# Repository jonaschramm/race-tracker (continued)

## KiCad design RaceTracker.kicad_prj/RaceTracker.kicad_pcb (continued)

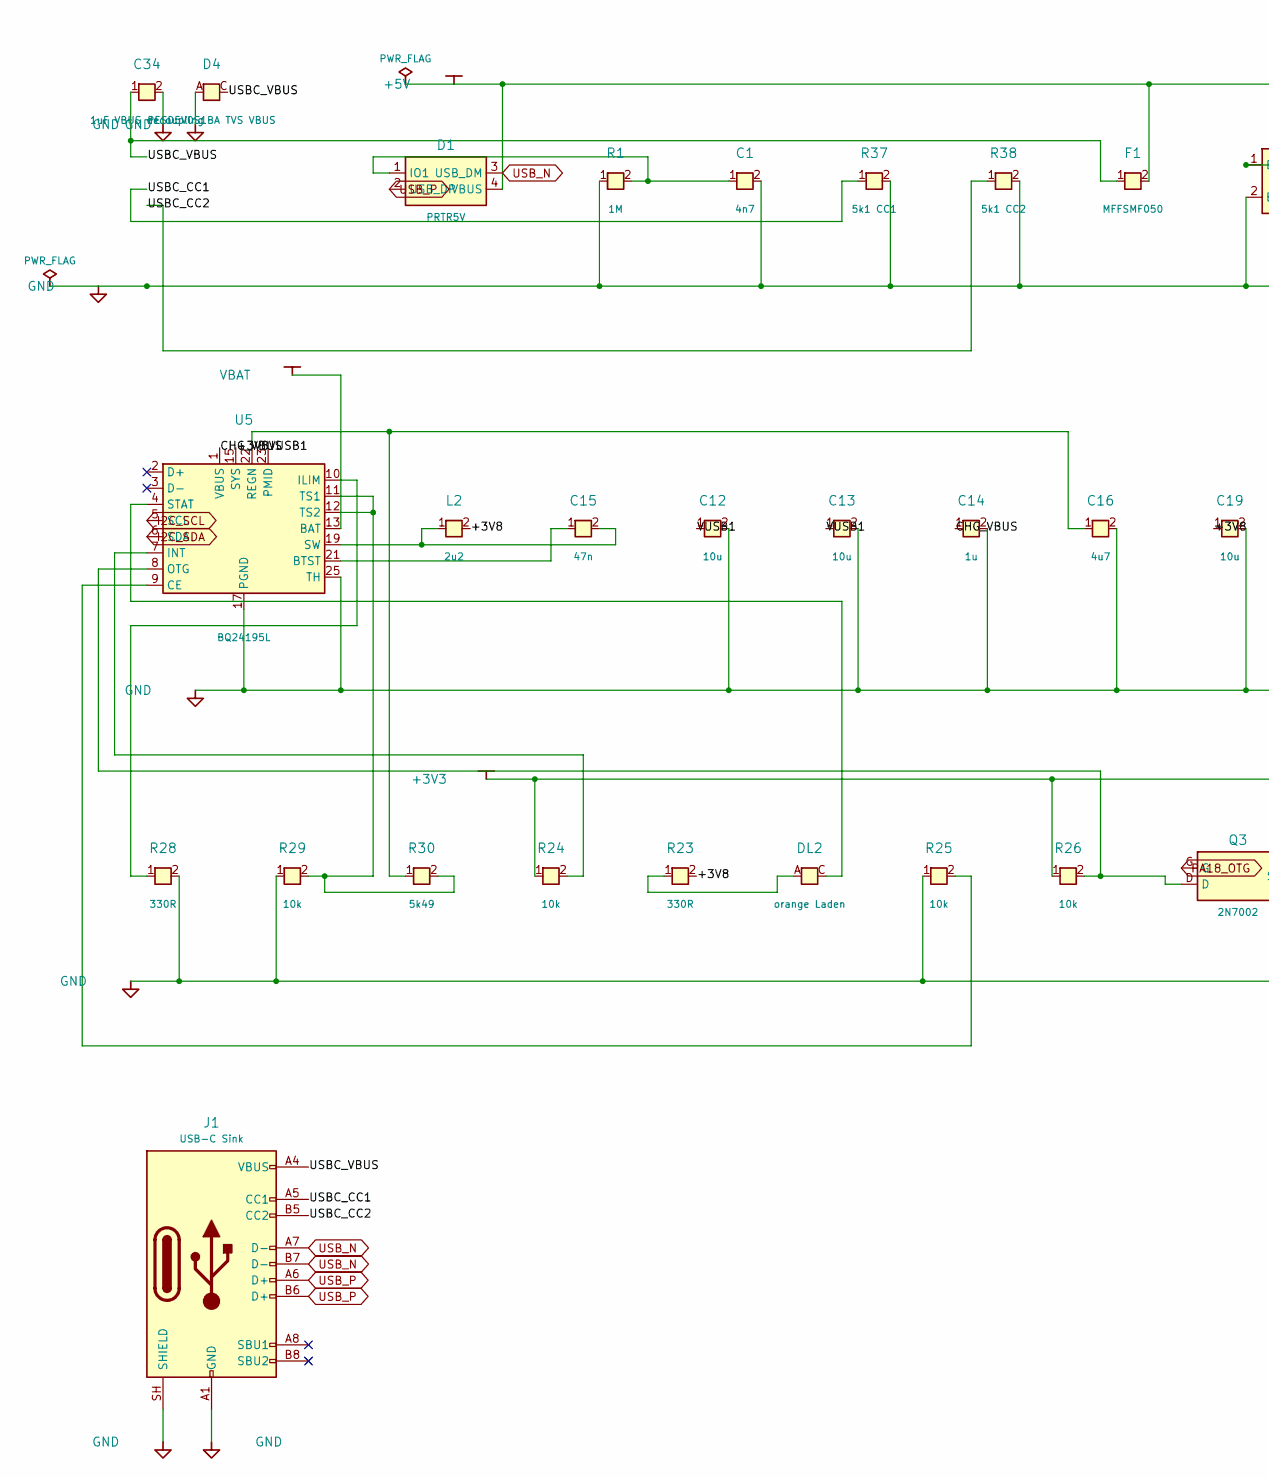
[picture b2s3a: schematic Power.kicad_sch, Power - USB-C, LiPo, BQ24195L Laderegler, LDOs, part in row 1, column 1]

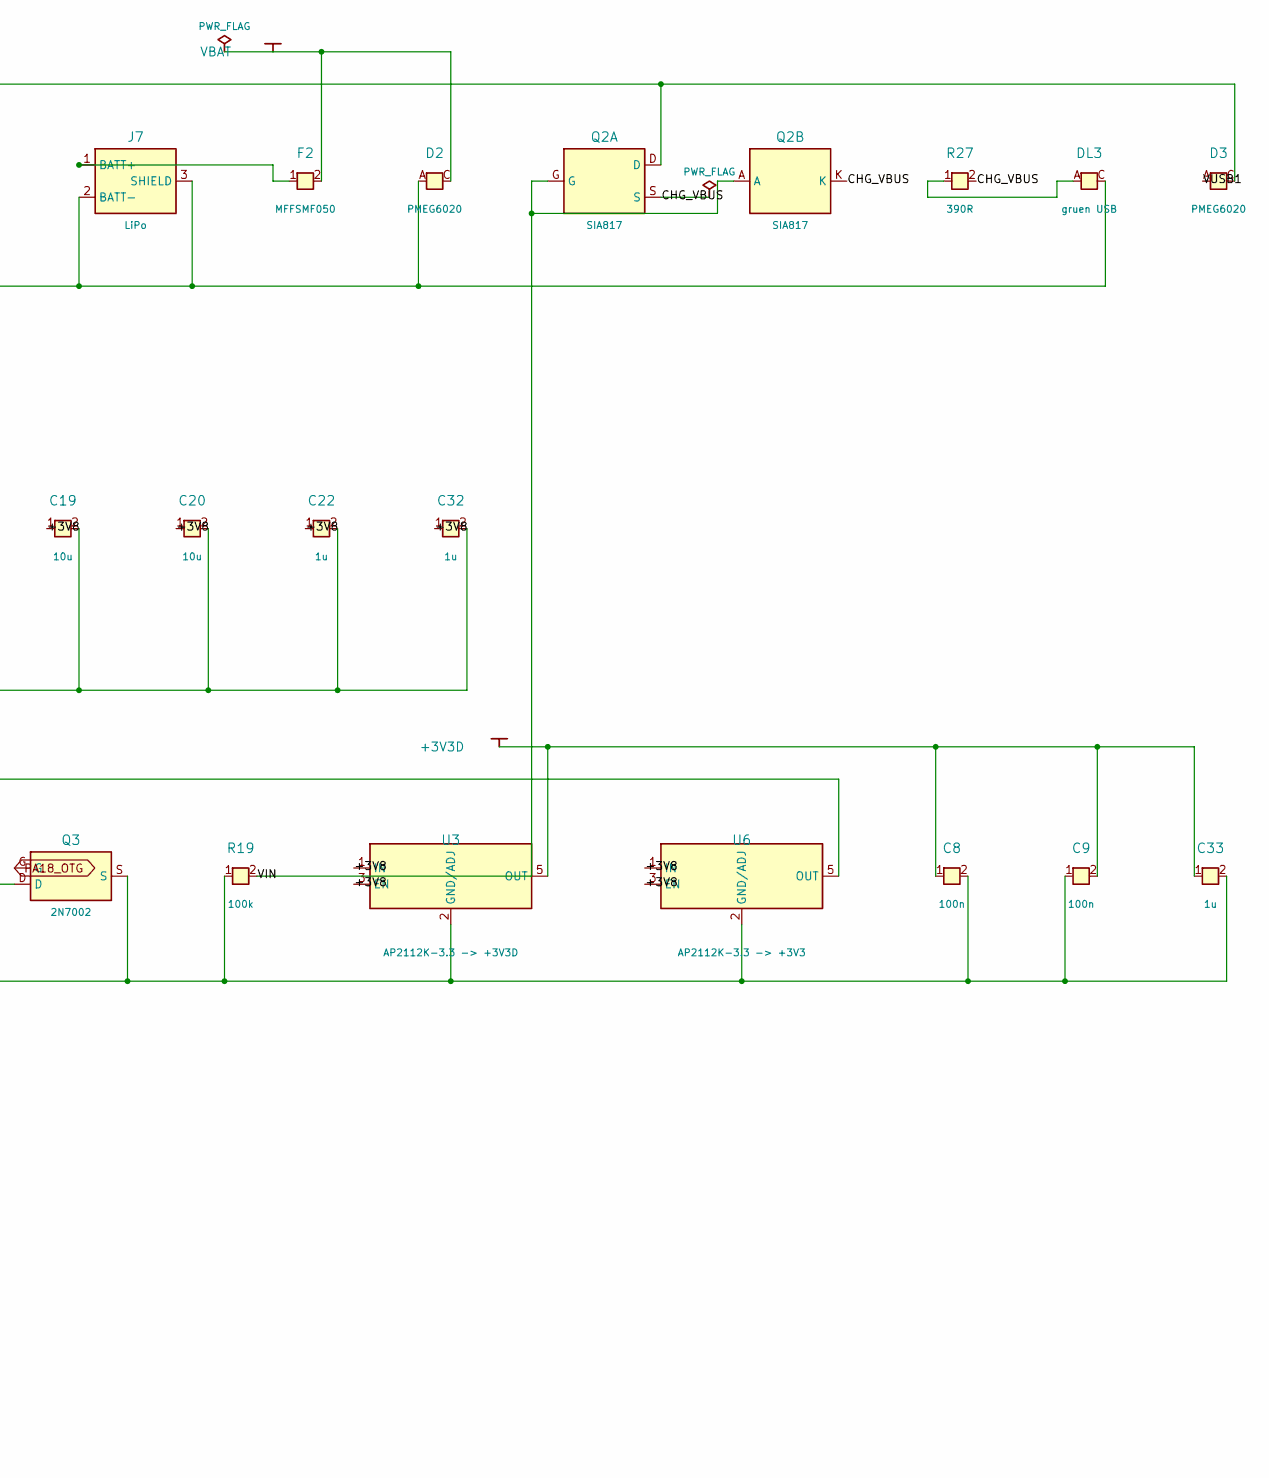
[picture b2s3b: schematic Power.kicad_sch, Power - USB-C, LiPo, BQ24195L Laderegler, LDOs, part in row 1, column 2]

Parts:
C1: 4n7; C_0805_2012Metric
C8, C9: 100n; C_0402_1005Metric
C12, C13, C19, C20: 10u; C_0603_1608Metric
C14, C22, C32, C33: 1u; C_0402_1005Metric
C15: 47n; C_0402_1005Metric
C16: 4u7; C_0402_1005Metric
C34: 1uF VBUS decoupling; C_0402_1005Metric
D1: PRTR5V; SOT143B_4N; MPN PRTR5V0U2X,215
D2, D3: PMEG6020; SODFL3517X110N
D4: PESD5V0S1BA TVS VBUS; D_SOD-323; MPN PESD5V0S1BA
DL2: orange Laden; LED_0603_AK
DL3: gruen USB; LED_0603_AK
F1, F2: MFFSMF050; Fuse_0603_1608Metric
J1: USB-C Sink; USB_C_Receptacle_HRO_TYPE-C-31-M-12; MPN TYPE-C-31-M-12
J7: LiPo; JST_S2B_PH_SM4_TB
L2: 2u2; SRP4020
Q2: SIA817; SON65P205X205X75-8N-MWSD
Q3: 2N7002; SOTFL50P160X78-3
R1: 1M; R_0402_1005Metric
R19: 100k; R_0402_1005Metric
R23, R28: 330R; R_0402_1005Metric
R24, R25, R26, R29: 10k; R_0402_1005Metric
R27: 390R; R_0402_1005Metric
R30: 5k49; R_0402_1005Metric
R37: 5k1 CC1; R_0402_1005Metric
R38: 5k1 CC2; R_0402_1005Metric
U3: AP2112K-3.3 -> +3V3D; SOT25
U5: BQ24195L; QFN24_BQ24195L
U6: AP2112K-3.3 -> +3V3; SOT25

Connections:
+3V3D: C8.1, C9.2, C33.1, U3.5 (OUT); also elsewhere on the board
/Power/+3V8: C19.1, C20.1, C22.1, C32.1, L2.2, R23.2, U3.1 (IN), U3.3 (EN), U5.15 (SYS), U5.16, U6.1 (IN), U6.3 (EN)
/Power/CHG_VBUS: C14.1, Q2.K, Q2.K2, Q2.S, R27.2, U5.1 (VBUS), U5.24
/Power/USBC_CC1: J1.A5 (CC1), R37.1
/Power/USBC_CC2: J1.B5 (CC2), R38.1
/Power/USBC_VBUS: C34.1, D4.C, F1.1, J1.A4 (VBUS), J1.A9 (VBUS), J1.B4 (VBUS), J1.B9 (VBUS)
/Power/VIN: Q2.A, Q2.G, R19.2
/Power/VUSB1: C12.1, C13.1, D3.A, U5.23 (PMID)
GND: C1.2, C8.2, C9.1, C12.2, C13.2, C14.2, C16.2, C19.2, C20.2, C22.2, C32.2, C33.2, C34.2, D2.A, D4.A, DL3.C, J1.A1 (GND), J1.A12 (GND), J1.B1 (GND), J1.B12 (GND), J1.SH (SHIELD), J7.2 (BATT-), J7.3 (SHIELD), J7.4 (SHIELD), Q3.S, R1.1, R19.1, R25.1, R28.2, R29.1, R37.2, R38.2, U3.2 (GND/ADJ), U5.17 (PGND), U5.18, U5.25 (TH), U6.2 (GND/ADJ); also elsewhere on the board
I2C_SCL: U5.5 (SCL); also elsewhere on the board
I2C_SDA: U5.6 (SDA); also elsewhere on the board
unnamed: C1.1, D1.1 (IO1), R1.2
unnamed: DL2.A, R23.1
unnamed: DL3.A, R27.1
unnamed: F2.1, J7.1 (BATT+)
unnamed: C15.1, U5.21 (BTST)
unnamed: R25.2, U5.9 (CE)
unnamed: R28.1, U5.10 (ILIM)
unnamed: R24.2, U5.7 (INT)
unnamed: Q3.D, R26.2, U5.8 (OTG)
unnamed: C16.1, R30.1, U5.22 (REGN)
unnamed: DL2.C, U5.4 (STAT)
unnamed: C15.2, L2.1, U5.19 (SW), U5.20
unnamed: R29.2, R30.2, U5.11 (TS1), U5.12 (TS2)
PA18_OTG: Q3.G; also elsewhere on the board
USB_P: D1.2 (USB_DP), J1.A6 (D+), J1.B6 (D+); also elsewhere on the board
VBAT: D2.C, F2.2, U5.13 (BAT), U5.14; also elsewhere on the board

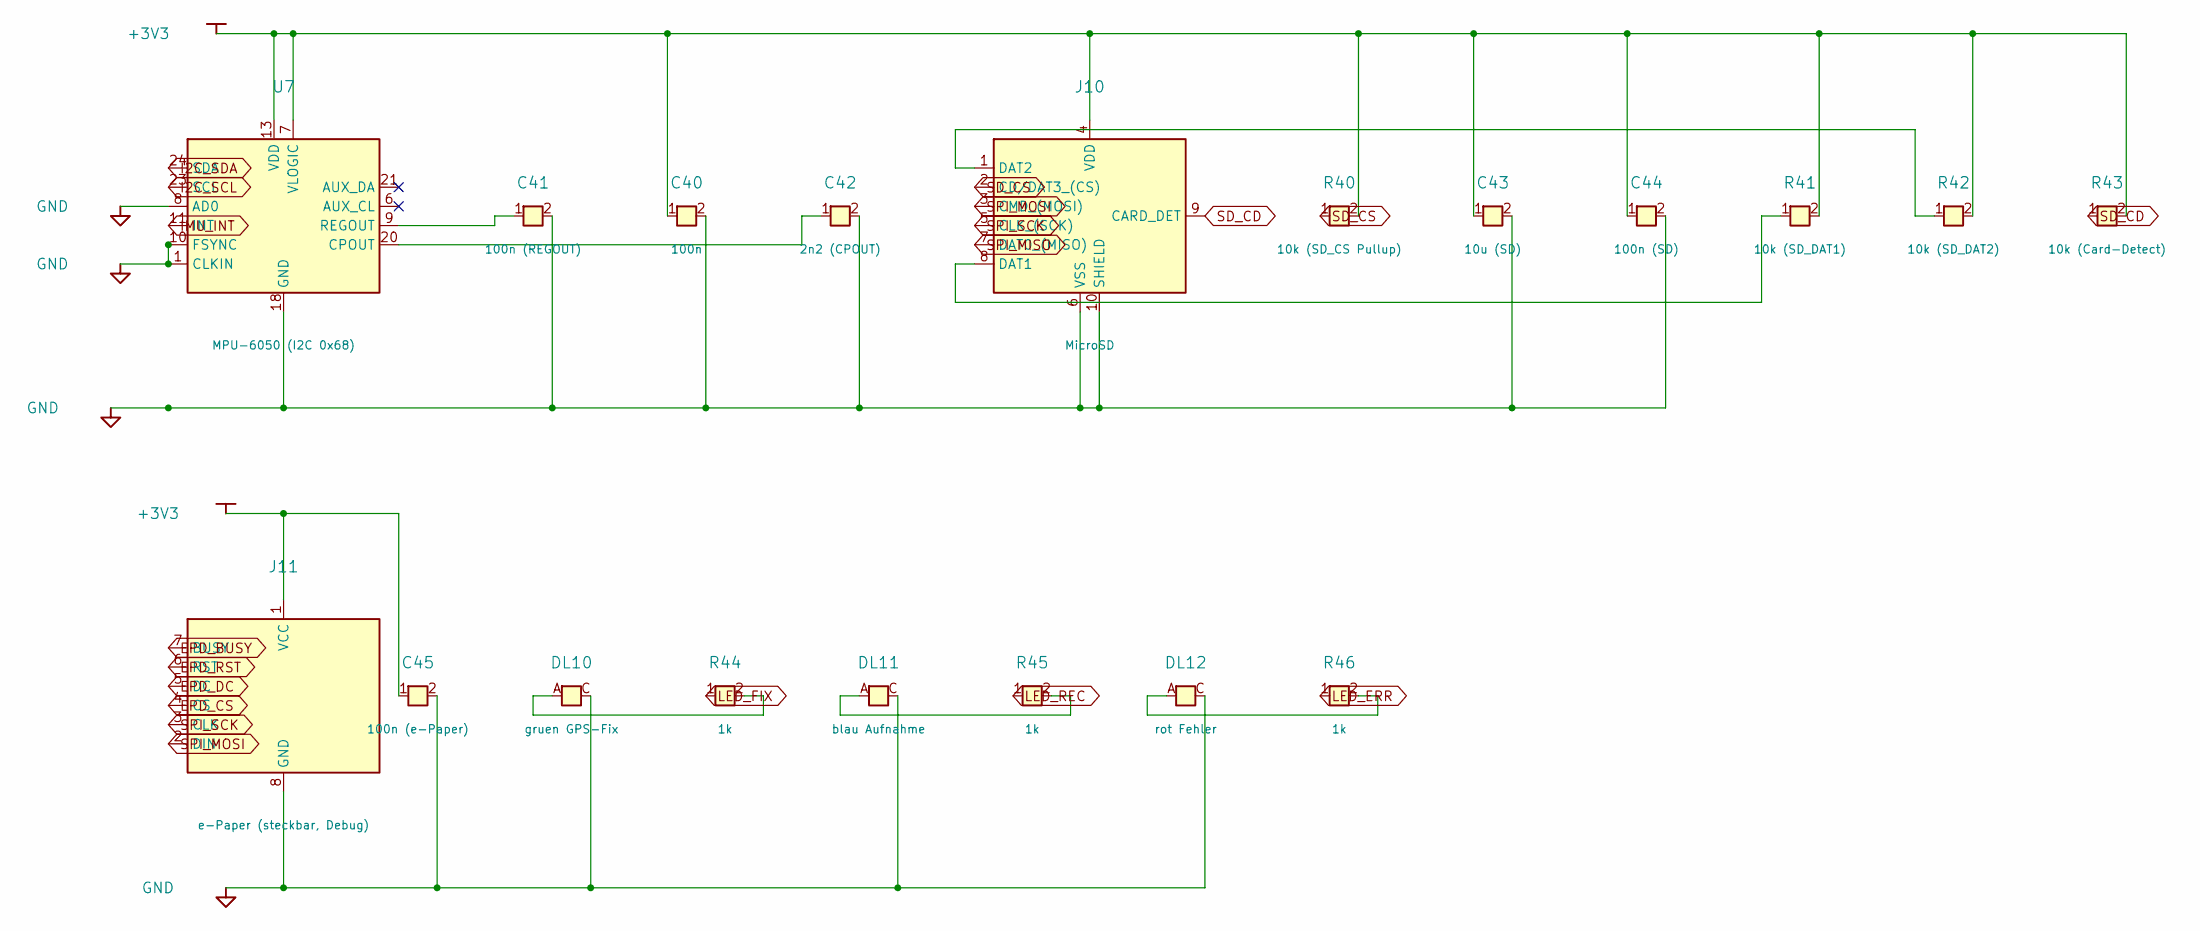
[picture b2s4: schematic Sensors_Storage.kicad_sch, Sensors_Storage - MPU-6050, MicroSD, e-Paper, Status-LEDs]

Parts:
C40: 100n; C_0402_1005Metric
C41: 100n (REGOUT); C_0402_1005Metric
C42: 2n2 (CPOUT); C_0402_1005Metric
C43: 10u (SD); C_0603_1608Metric
C44: 100n (SD); C_0402_1005Metric
C45: 100n (e-Paper); C_0402_1005Metric
DL10: gruen GPS-Fix; LED_0603_AK
DL11: blau Aufnahme; LED_0603_AK
DL12: rot Fehler; LED_0603_AK
J10: MicroSD; microSD_HC_Molex_104031-0811
J11: e-Paper (steckbar, Debug); PinHeader_1x08_P2.54mm_Vertical
R40: 10k (SD_CS Pullup); R_0402_1005Metric
R41: 10k (SD_DAT1); R_0402_1005Metric
R42: 10k (SD_DAT2); R_0402_1005Metric
R43: 10k (Card-Detect); R_0402_1005Metric
R44, R45, R46: 1k; R_0402_1005Metric
U7: MPU-6050 (I2C 0x68); InvenSense_QFN-24_4x4mm_P0.5mm

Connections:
EPD_BUSY: J11.7 (BUSY); also elsewhere on the board
EPD_CS: J11.4 (CS); also elsewhere on the board
EPD_DC: J11.5 (DC); also elsewhere on the board
EPD_RST: J11.6 (RST); also elsewhere on the board
GND: C40.2, C41.2, C42.2, C43.2, C44.2, C45.2, DL10.C, DL11.C, DL12.C, J10.6 (VSS), J10.10 (SHIELD), J11.8 (GND), U7.1 (CLKIN), U7.8 (AD0), U7.10 (FSYNC), U7.18 (GND); also elsewhere on the board
I2C_SCL: U7.23 (SCL); also elsewhere on the board
I2C_SDA: U7.24 (SDA); also elsewhere on the board
IMU_INT: U7.11 (INT); also elsewhere on the board
LED_ERR: R46.1; also elsewhere on the board
LED_FIX: R44.1; also elsewhere on the board
LED_REC: R45.1; also elsewhere on the board
unnamed: DL10.A, R44.2
unnamed: DL11.A, R45.2
unnamed: DL12.A, R46.2
unnamed: J10.8 (DAT1), R41.1
unnamed: J10.1 (DAT2), R42.1
unnamed: C42.1, U7.20 (CPOUT)
unnamed: C41.1, U7.9 (REGOUT)
SD_CD: J10.9 (CARD_DET), R43.1; also elsewhere on the board
SD_CS: J10.2 (CD/DAT3_(CS)), R40.1; also elsewhere on the board
SPI_MISO: J10.7 (DAT0_(MISO)); also elsewhere on the board
SPI_MOSI: J10.3 (CMD_(MOSI)), J11.2 (DIN); also elsewhere on the board
SPI_SCK: J10.5 (CLK_(SCK)), J11.3 (CLK); also elsewhere on the board

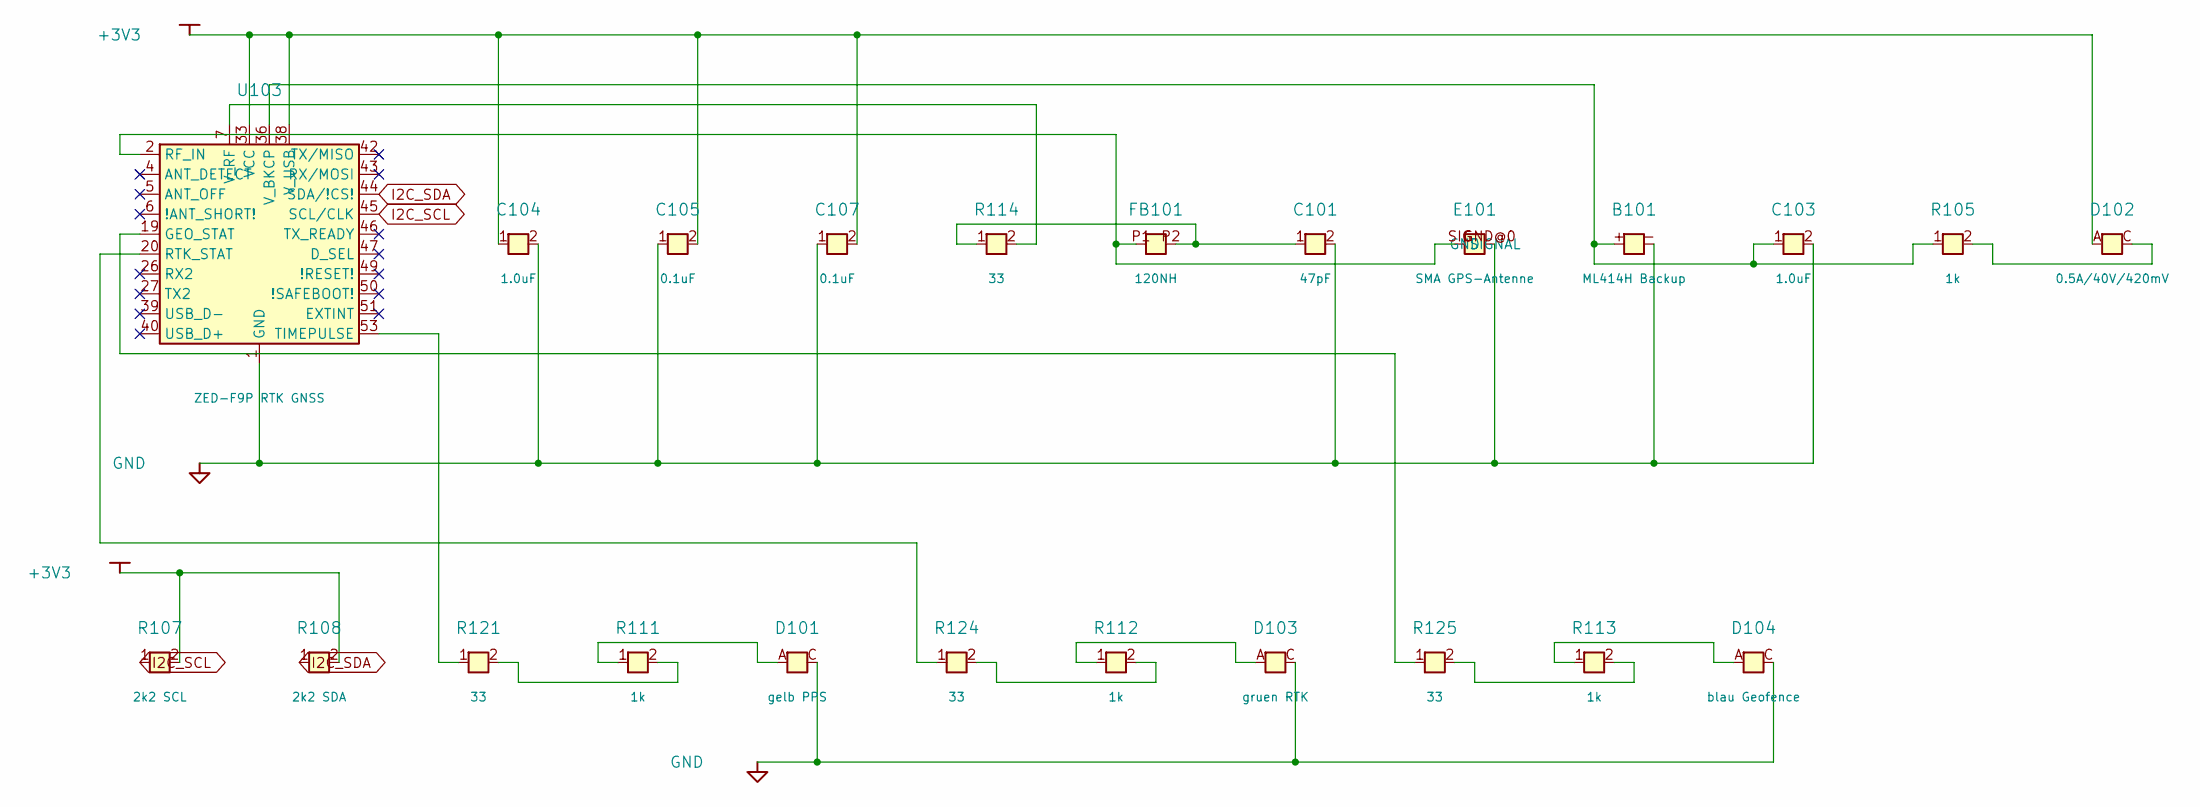
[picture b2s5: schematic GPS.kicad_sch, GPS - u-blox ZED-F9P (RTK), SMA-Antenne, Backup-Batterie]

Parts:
B101: ML414H Backup; ML414H_COIN_CELL
C101: 47pF; C_0402_1005Metric
C103, C104: 1.0uF; C_0402_1005Metric
C105, C107: 0.1uF; C_0402_1005Metric
D101: gelb PPS; LED_0603_AK
D102: 0.5A/40V/420mV; SODFL3517X110N
D103: gruen RTK; LED_0603_AK
D104: blau Geofence; LED_0603_AK
E101: SMA GPS-Antenne; SMA_EDGE
FB101: 120NH; L_0402_1005Metric
R105, R111, R112, R113: 1k; R_0402_1005Metric
R107: 2k2 SCL; R_0402_1005Metric
R108: 2k2 SDA; R_0402_1005Metric
R114, R121, R124, R125: 33; R_0402_1005Metric
U103: ZED-F9P RTK GNSS; ZED_F9P_LGA102

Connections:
GND: B101.-, C101.2, C103.2, C104.2, C105.1, C107.1, D101.C, D103.C, D104.C, E101.GND@0 (GND), E101.GND@1 (GND), E101.GND@2 (GND), E101.GND@3 (GND), U103.1 (GND), U103.3, U103.12, U103.14, U103.32, U103.37, U103.41, U103.48, U103.55, U103.56, U103.57, U103.58, U103.59, U103.60, U103.61, U103.62, U103.63, U103.64, U103.65, U103.66, U103.67, U103.68, U103.69, U103.70, U103.71, U103.72, U103.73, U103.74, U103.75, U103.76, U103.77, U103.78, U103.79, U103.80, U103.81, U103.82, U103.83, U103.84, U103.85, U103.86, U103.87, U103.88, U103.89, U103.90, U103.91, U103.92, U103.93, U103.94, U103.95, U103.96, U103.97, U103.98, U103.99, U103.100, U103.101, U103.102; also elsewhere on the board
I2C_SCL: R107.1, U103.45 (SCL/CLK); also elsewhere on the board
I2C_SDA: R108.1, U103.44 (SDA/!CS!); also elsewhere on the board
unnamed: C101.1, FB101.P2, R114.1
unnamed: D101.A, R111.1
unnamed: D102.C, R105.2
unnamed: D103.A, R112.1
unnamed: D104.A, R113.1
unnamed: E101.SIG (SIGNAL), FB101.P1, U103.2 (RF_IN)
unnamed: R111.2, R121.2
unnamed: R112.2, R124.2
unnamed: R113.2, R125.2
unnamed: R125.1, U103.19 (GEO_STAT)
unnamed: R124.1, U103.20 (RTK_STAT)
unnamed: R121.1, U103.53 (TIMEPULSE)
unnamed: B101.+, C103.1, R105.1, U103.36 (V_BKCP)
unnamed: R114.2, U103.7 (V_RF)

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
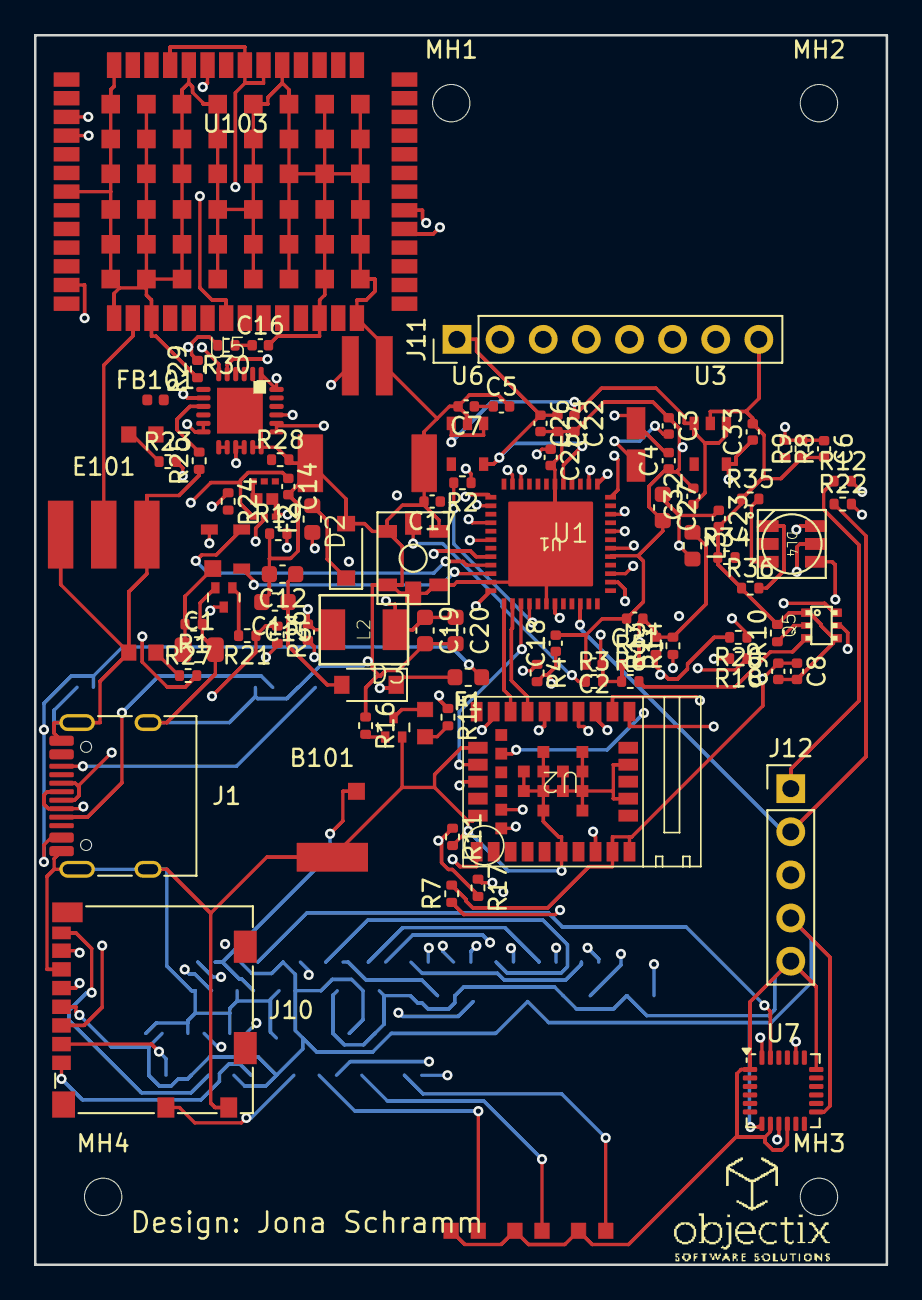
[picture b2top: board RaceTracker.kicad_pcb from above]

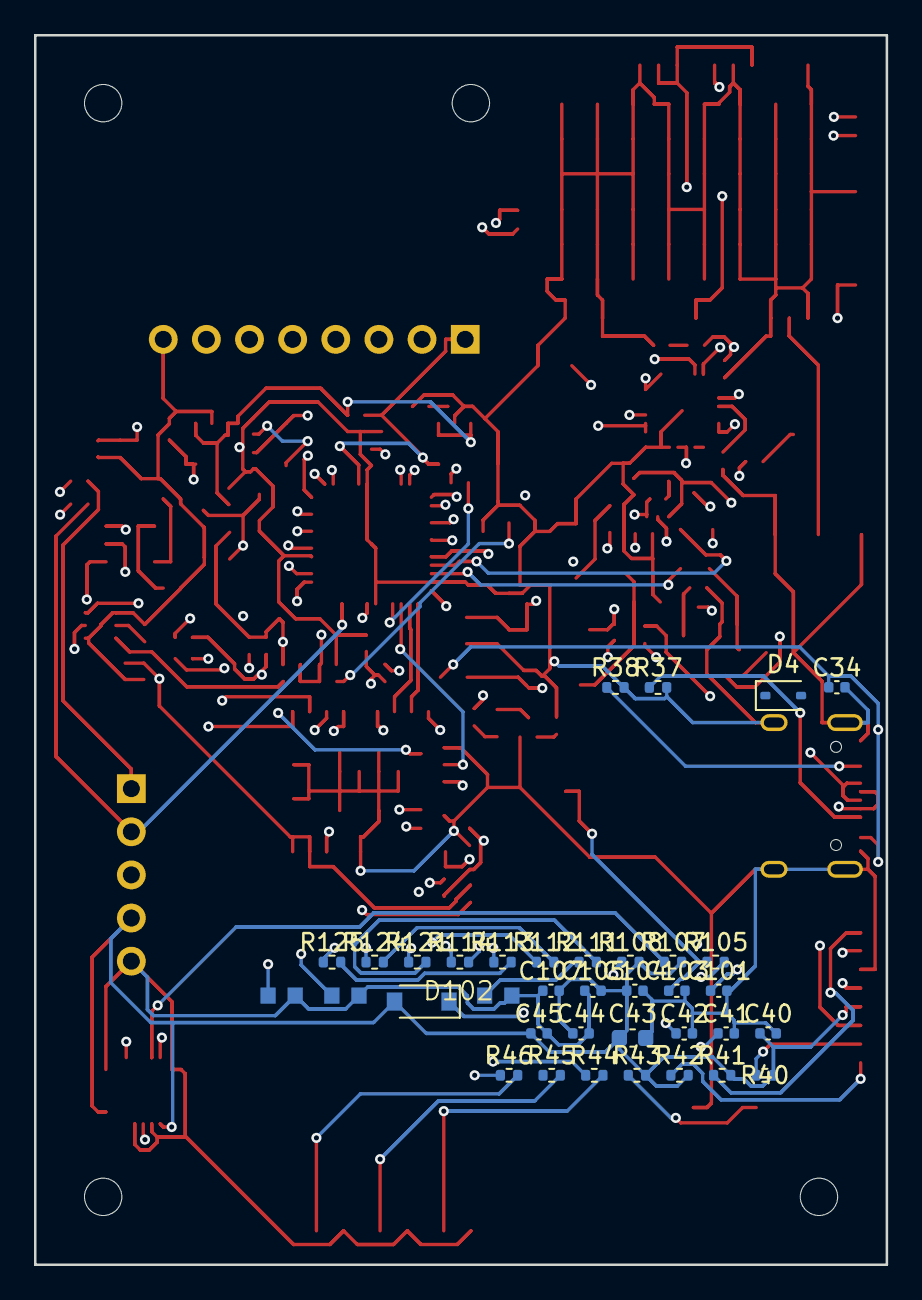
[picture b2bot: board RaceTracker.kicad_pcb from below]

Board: 4 copper layers, 50.2 x 72.4 mm, 135 parts (36 on the bottom side), 101 nets.

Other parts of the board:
MH1, MH2, MH3, MH4: MountingHole_2.2mm_M2

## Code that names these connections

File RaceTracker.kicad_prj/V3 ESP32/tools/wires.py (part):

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tap_label("R11", "1", "+3V3", 0, -STUB)
tap_label("J3", "1", "GND", -STUB, 0)
tap_label("J3", "2", "+3V3", -STUB, 0)
tap_label("J3", "3", "I2C_SDA", STUB, 0)
tap_label("J3", "4", "I2C_SCL", STUB, 0)

# ===========================================================================
# SPI to the microSD socket: same pattern. J4's real pinout interleaves
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# ===========================================================================
signal_through("U1", "18", "R12", "2", "SD_CS", (-2.54, 0), mod_stub=-2.54)
tap_label("R12", "1", "+3V3", 0, -STUB)
tap_label("U1", "19", "SD_MOSI", -11.43, 0)   # no pull-up needed
tap_label("U1", "20", "SD_SCK", -20.32, 0)
signal_through("U1", "21", "R13", "2", "SD_MISO", (-2.54, 0), mod_stub=-29.21)
tap_label("R13", "1", "+3V3", 0, -STUB)
signal_through("U1", "22", "R14", "2", "SD_CD", (-2.54, 0), mod_stub=-38.1)
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# Pins 2-7 are six pins in a row, each only 2.54mm apart -- every one gets
# a longer stub than the last so none of the six labels land in the same
# column (same reasoning as U1's own pin stubs above).
tap_label("J4", "2", "SD_CS", -7.62, 0)
tap_label("J4", "3", "SD_MOSI", -16.51, 0)
tap_label("J4", "4", "+3V3", -25.4, 0)      # VDD
tap_label("J4", "5", "SD_SCK", -34.29, 0)
tap_label("J4", "6", "GND", -43.18, 0)      # VSS
tap_label("J4", "7", "SD_MISO", -52.07, 0)
tap_label("J4", "9", "GND", -7.62, 0)       # DET_B (other detect-switch leg)
tap_label("J4", "10", "SD_CD", -16.51, 0)
tap_label("J4", "SH", "GND", 0, STUB)       # shield tab
nc("J4", "1")   # DAT2 unused in SPI mode
nc("J4", "8")   # DAT1 unused in SPI mode
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# USB-C/battery/LDO cluster, so route via labels rather than a routed run
# through that territory.
# ===========================================================================
tap_label("U1", "37", "DBG_TXD0", STUB, 0)
# down+right (an L, not a diagonal): straight right runs into D1's VBUS stub.
_rxd0_p0 = P("U1", "36")
_rxd0_p1 = (_rxd0_p0[0] + STUB, _rxd0_p0[1])
_rxd0_p2 = (_rxd0_p1[0], _rxd0_p1[1] + 5.08)
wire(_rxd0_p0, _rxd0_p1, _rxd0_p2)
label(_rxd0_p2, "DBG_RXD0", dir="down")
tap_label("J5", "4", "DBG_TXD0", -STUB, 0)
# down+left (an L, not a diagonal): a longer straight-left reach runs into D1.
_j5rxd0_p0 = P("J5", "3")
_j5rxd0_p1 = (_j5rxd0_p0[0] - STUB, _j5rxd0_p0[1])
_j5rxd0_p2 = (_j5rxd0_p1[0], _j5rxd0_p1[1] + 5.08)
wire(_j5rxd0_p0, _j5rxd0_p1, _j5rxd0_p2)
label(_j5rxd0_p2, "DBG_RXD0", dir="down")
tap_label("J5", "2", "+3V3", STUB, 0)
tap_label("J5", "1", "GND", STUB, 0)

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# J1 and D1 are ~80mm apart across the CC-pulldown/VBUS-decoupling area --
# a routed wire there would have to cross that whole cluster, so this is
# label-only (same reasoning as D1<->U1 below).
tap_label("J1", "A6", "USB_DP", STUB, 0)  # A6/A7 are 5.08mm apart -- fine as-is
wire(P("D1", "1"), P("D1", "6"))                              # duplicate I/O1 pin, same node
JUNCTIONS.append(P("D1", "1"))
tap_label("D1", "1", "USB_DP", -STUB, 0)  # D1.1/D1.3 (I/O1/I/O2) are 2.54mm apart

tap_label("J1", "A7", "USB_DM", STUB, 0)
wire(P("D1", "3"), P("D1", "4"))                              # duplicate I/O2 pin, same node
JUNCTIONS.append(P("D1", "3"))
tap_label("D1", "3", "USB_DM", -STUB - 12.7, 0)

tap_label("U1", "14", "USB_DP", STUB, 0)
tap_label("U1", "13", "USB_DM", STUB + 12.7, 0)

nc("J1", "A8")   # SBU1 -- not used (no USB-C alt-mode/accessory support)
nc("J1", "B8")   # SBU2
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# elbow was ordered (confirmed via check_nets.py -- e.g. the STAT->LED
# run at LED-cathode height clipped the PROG resistor's own stub a few mm
# over). Same fix as the bus signals: label instead of routing through it.
tap_label("U2", "1", "CHG_STAT", STUB, 0)   # right, not up -- U2.3 (VBAT) shares this
                                             # X 5.08mm below and also stubs upward
tap_label("D2", "1", "CHG_STAT", -STUB, 0)
tap_label("D2", "2", "CHG_LED_A", STUB, 0)              # LED anode -> series R (label: D2 is
tap_label("R4", "1", "CHG_LED_A", 0, -STUB)             # horizontal, R4 vertical -- pins don't line up)
tap_label("R4", "2", "+VBUS", 0, STUB)                  # opposite direction from pin 1 (only
                                                         # 7.62mm apart -- same-direction stubs overlap)
tap_label("U2", "5", "CHG_PROG", 0, -STUB)  # up, not down -- avoids D2's CHG_LED_A stub row
tap_label("R3", "1", "CHG_PROG", 0, -STUB)
tap_label("R3", "2", "GND", 0, STUB)

tap_label("U2", "2", "GND", -STUB, 0)
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tap_label("C5", "1", "+3V3", 0, -STUB)
tap_label("C5", "2", "GND", 0, STUB)
tap_label("R5", "1", "+3V3", 0, -STUB)
tap_label("R5", "2", "PWR_LED_A", 0, STUB)              # series R -> LED anode (label: R5 is
tap_label("D3", "2", "PWR_LED_A", STUB, 0)              # vertical, D3 horizontal -- pins don't line up)
tap_label("D3", "1", "GND", 0, STUB)

# ===========================================================================
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wire(P("R6", "2"), P("C6", "1"))      # midpoint -> filter cap, direct
tap_label("R7", "2", "GND", 0, STUB)
tap_label("C6", "2", "GND", 0, STUB)
tap_label("R6", "2", "BATT_SENSE", STUB, 0)
tap_label("U1", "28", "BATT_SENSE", STUB, 0)

# ===========================================================================
# Module's own power pins + bulk/HF decoupling
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
# ===========================================================================
# No-connects: strapping pins left floating per datasheet default (Table
# 4-1: GPIO3 floating, GPIO45/46 weak pull-down = correct default for this
# non-PSRAM, 3.3V-VDD_SPI module -- see peripheral schematic, Fig. 9-1,
# which leaves these bare too), plus every other genuinely free GPIO
# (rule 32: kicad-cli ERC treats a bare bidirectional MCU pin as a real
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
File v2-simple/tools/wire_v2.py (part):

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mit BQ24195L geteilt, exakt wie ZED-F9P in v1) -- TX/RX/PPS/RESET bleiben
No-Connect, da es dafuer keine v1-Entsprechung zum MCU gibt (die eigentliche
GPS-Verkabelung folgt separat, wenn das externe Modul angeschlossen wird).
J22 uebernimmt die SERCOM-Pins, die in v1 an NINA-W102 hingen (PB22/PB23 =
UART, PA14/PA15 = RTS/CTS); RESET/EN bleiben No-Connect (kein sauberer
v1-Fund fuer die durch den entfallenen Pegelwandler Q5 gefuehrte
Reset-Leitung). J21 uebernimmt 1:1 die Pin-Netze von v1s J11.

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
